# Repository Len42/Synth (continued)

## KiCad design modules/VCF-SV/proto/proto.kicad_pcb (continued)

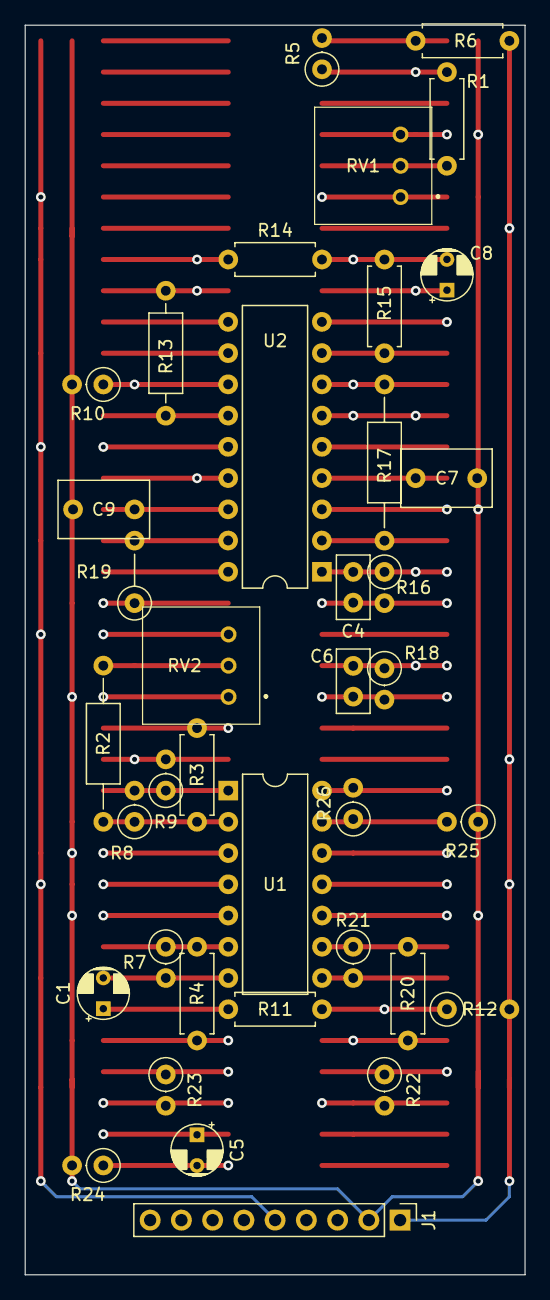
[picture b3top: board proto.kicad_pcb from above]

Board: 6 copper layers, 40.6 x 101.6 mm, 38 parts (0 on the bottom side), 31 nets.

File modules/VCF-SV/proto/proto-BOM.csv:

Ref,Qty,Value,Value2,Note,Description,Datasheet,Manufacturer,ManuPartNum,Distributor1,DistributorPartNum1,DistributorPartLink1,Distributor2,DistributorPartNum2,DistributorPartLink2,Distributor3,DistributorPartNum3,DistributorPartLink3
"C1 C5 C8","3","4U7","","","Capacitor - Electrolytic","","","","","","","","","","","",""
"C2 C3","2","100N","","DNP","Capacitor - Ceramic - IC decoupling","https://product.tdk.com/system/files/dam/doc/product/capacit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","TDK","FG18X7R1H104KNT06","Mouser","810-FG18X7R1H104KNT6","https://www.mouser.ca/ProductDetail/810-FG18X7R1H104KNT6","","","","","",""
"C4","1","10P","","","Capacitor - Ceramic","","","","","","","","","","","",""
"C6","1","18P","","","Capacitor - Ceramic","","","","","","","","","","","",""
"C7 C9","2","150P","","","Capacitor - Film","","","","","","","","","","","",""
"R1","1","130K","1%, 1/6 W","*changed","Resistor","https://www.mouser.ca/datasheet/2/447/Yageo_LR_MFR_1-1714151.pdf","YAGEO","MFR-12*","Mouser","603-MFR-12*","https://www.mouser.ca/c/?m=YAGEO&power+rating=166+mW+(1%2f6+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","","","","","",""
"R2","1","120K","1%, 1/6 W","","Resistor","https://www.mouser.ca/datasheet/2/447/Yageo_LR_MFR_1-1714151.pdf","YAGEO","MFR-12*","Mouser","603-MFR-12*","https://www.mouser.ca/c/?m=YAGEO&power+rating=166+mW+(1%2f6+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","","","","","",""
"R3","1","150K","","","Resistor","https://www.mouser.ca/datasheet/2/447/Yageo_LR_MFR_1-1714151.pdf","YAGEO","MFR-12*","Mouser","603-MFR-12*","https://www.mouser.ca/c/?m=YAGEO&power+rating=166+mW+(1%2f6+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","","","","","",""
"R4","1","200K","1%, 1/6 W","*changed","Resistor","https://www.mouser.ca/datasheet/2/447/Yageo_LR_MFR_1-1714151.pdf","YAGEO","MFR-12*","Mouser","603-MFR-12*","https://www.mouser.ca/c/?m=YAGEO&power+rating=166+mW+(1%2f6+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","","","","","",""
"R5 R24","2","1M","1%, 1/6 W","","Resistor","https://www.mouser.ca/datasheet/2/447/Yageo_LR_MFR_1-1714151.pdf","YAGEO","MFR-12*","Mouser","603-MFR-12*","https://www.mouser.ca/c/?m=YAGEO&power+rating=166+mW+(1%2f6+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","","","","","",""
"R6","1","1M5","1%, 1/6 W","","Resistor","https://www.mouser.ca/datasheet/2/447/Yageo_LR_MFR_1-1714151.pdf","YAGEO","MFR-12*","Mouser","603-MFR-12*","https://www.mouser.ca/c/?m=YAGEO&power+rating=166+mW+(1%2f6+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","","","","","",""
"R7 R8 R16 R17 R19 R21 R25 R26","8","100K","1%, 1/6 W","","Resistor","https://www.mouser.ca/datasheet/2/447/Yageo_LR_MFR_1-1714151.pdf","YAGEO","MFR-12*","Mouser","603-MFR-12*","https://www.mouser.ca/c/?m=YAGEO&power+rating=166+mW+(1%2f6+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","","","","","",""
"R9","1","43K","1%, 1/6 W","*changed","Resistor","https://www.mouser.ca/datasheet/2/447/Yageo_LR_MFR_1-1714151.pdf","YAGEO","MFR-12*","Mouser","603-MFR-12*","https://www.mouser.ca/c/?m=YAGEO&power+rating=166+mW+(1%2f6+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","","","","","",""
"R10","1","1K","1%, 1/6 W","","Resistor","https://www.mouser.ca/datasheet/2/447/Yageo_LR_MFR_1-1714151.pdf","YAGEO","MFR-12*","Mouser","603-MFR-12*","https://www.mouser.ca/c/?m=YAGEO&power+rating=166+mW+(1%2f6+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","","","","","",""
"R11 R18","2","91K","use 100K||1M","","Resistor","https://www.mouser.ca/datasheet/2/447/Yageo_LR_MFR_1-1714151.pdf","YAGEO","MFR-12*","Mouser","603-MFR-12*","https://www.mouser.ca/c/?m=YAGEO&power+rating=166+mW+(1%2f6+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","","","","","",""
"R12","1","300K","1%, 1/6 W","","Resistor","https://www.mouser.ca/datasheet/2/447/Yageo_LR_MFR_1-1714151.pdf","YAGEO","MFR-12*","Mouser","603-MFR-12*","https://www.mouser.ca/c/?m=YAGEO&power+rating=166+mW+(1%2f6+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","","","","","",""
"R13","1","1K2","1%, 1/6 W","","Resistor","https://www.mouser.ca/datasheet/2/447/Yageo_LR_MFR_1-1714151.pdf","YAGEO","MFR-12*","Mouser","603-MFR-12*","https://www.mouser.ca/c/?m=YAGEO&power+rating=166+mW+(1%2f6+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","","","","","",""
"R14","1","240K","1%, 1/6 W","","Resistor","https://www.mouser.ca/datasheet/2/447/Yageo_LR_MFR_1-1714151.pdf","YAGEO","MFR-12*","Mouser","603-MFR-12*","https://www.mouser.ca/c/?m=YAGEO&power+rating=166+mW+(1%2f6+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","","","","","",""
"R15","1","220K","1%, 1/6 W","","Resistor","https://www.mouser.ca/datasheet/2/447/Yageo_LR_MFR_1-1714151.pdf","YAGEO","MFR-12*","Mouser","603-MFR-12*","https://www.mouser.ca/c/?m=YAGEO&power+rating=166+mW+(1%2f6+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","","","","","",""
"R20","1","68K","1%, 1/6 W","*changed","Resistor","https://www.mouser.ca/datasheet/2/447/Yageo_LR_MFR_1-1714151.pdf","YAGEO","MFR-12*","Mouser","603-MFR-12*","https://www.mouser.ca/c/?m=YAGEO&power+rating=166+mW+(1%2f6+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","","","","","",""
"R22 R23","2","47K","1%, 1/6 W","","Resistor","https://www.mouser.ca/datasheet/2/447/Yageo_LR_MFR_1-1714151.pdf","YAGEO","MFR-12*","Mouser","603-MFR-12*","https://www.mouser.ca/c/?m=YAGEO&power+rating=166+mW+(1%2f6+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","","","","","",""
"RV1 RV2","2","100K","LIN","","Potentiometer","","","","","","","","","","","",""
"U1","1","TL074","","","Quad Low-Noise JFET-Input Operational Amplifiers, DIP-14/SOIC-14","http://www.ti.com/lit/ds/symlink/tl071.pdf","Texas Instruments","TL074BCN","Mouser","595-TL074BCN","https://www.mouser.ca/ProductDetail/?qs=vxEfx8VrU7BHurOY5iQd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","","","","","",""
"U2","1","CEM3320","","or AS3320","Voltage Controlled Filter (VCF), DIP-18","https://electricdruid.net/wp-content/uploads/2017/06/CEM3320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","Curtis Electromusic","3320","Thonk","EComp_Chip_CURTIS_CEM3320","https://www.thonk.co.uk/shop/cem3320/","Electric Druid","AS3320","https://electricdruid.net/product/as3320-vcf/","SynthCube","ARAS3320MSTR","https://synthcube.com/cart/synth-diy/parts/ics-and-semicondu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"
